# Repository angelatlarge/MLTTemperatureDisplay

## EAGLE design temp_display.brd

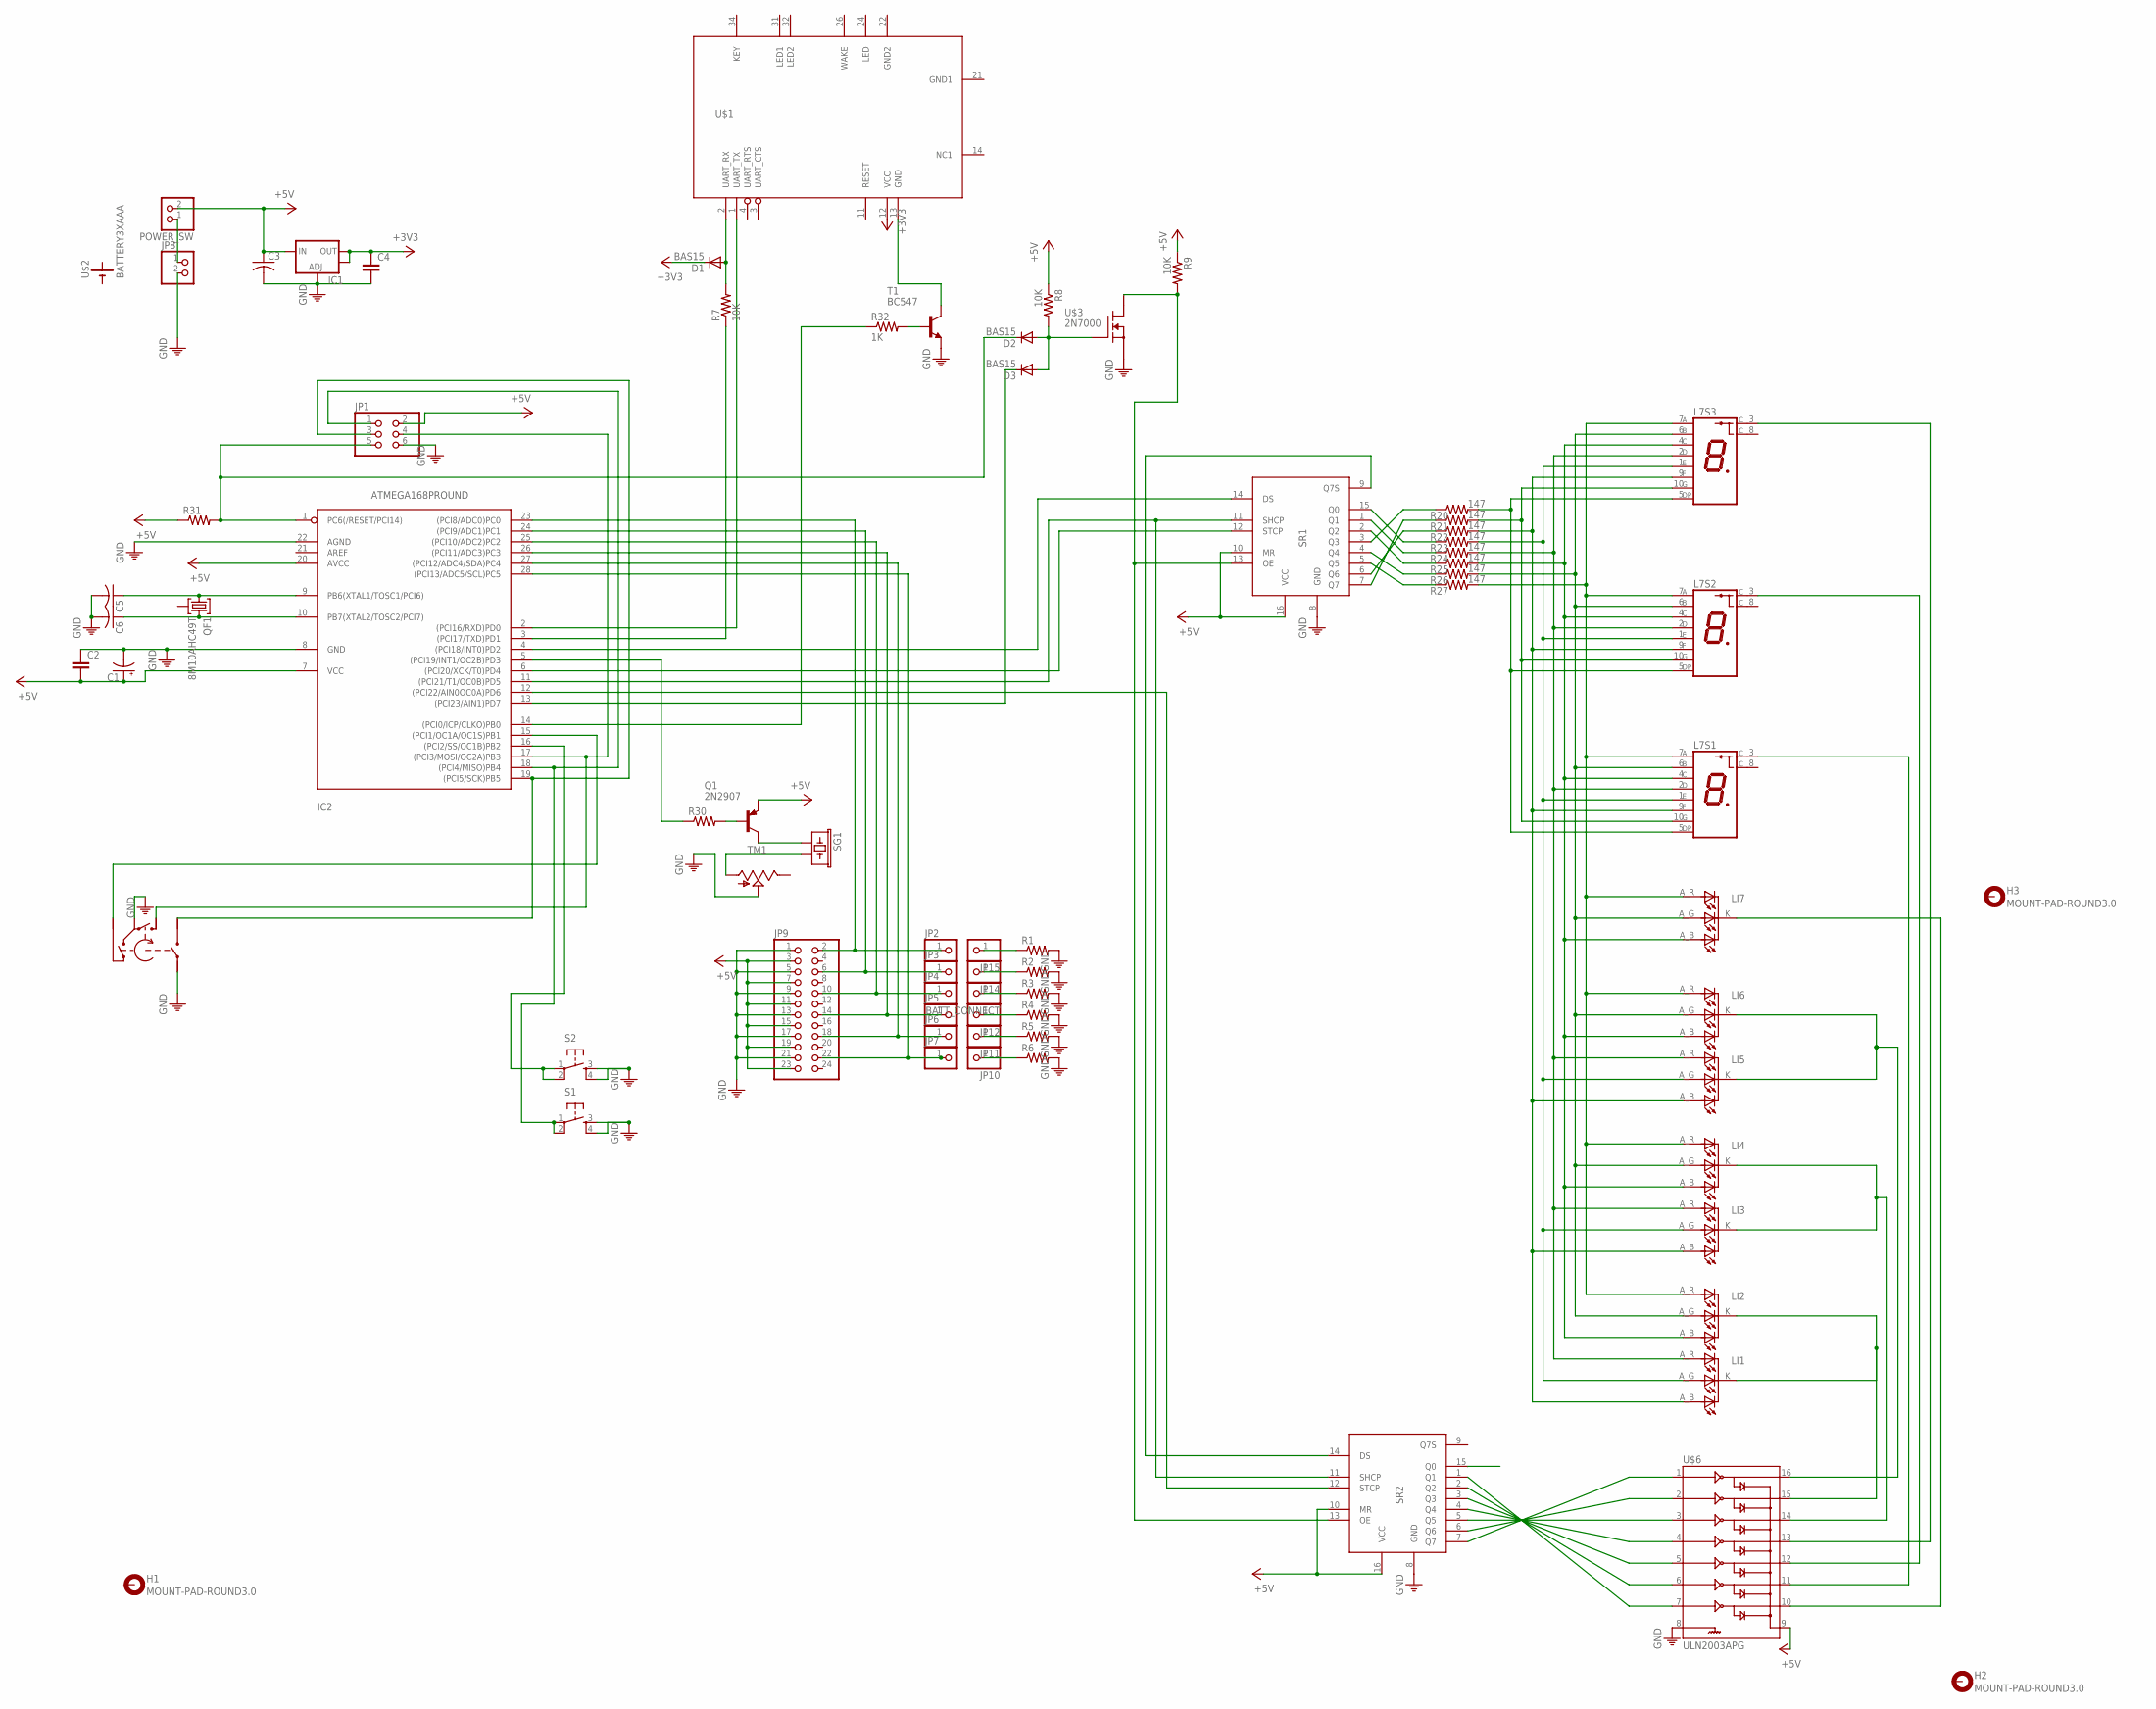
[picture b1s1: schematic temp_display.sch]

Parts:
BATT_CONNECT: PINHD-1X1; 1X01
C1: CPOL-USE2.5-5; E2,5-5
C2: CAPPTH1; CAP-PTH-5MM
C3: C-US050-025X075; C050-025X075
C4: CAPSMD; GRM43D
C5, C6: C-US025-024X044; C025-024X044
D1, D2, D3: BAS15; DO34-7
H1, H2, H3: MOUNT-PAD-ROUND3.0; 3,0-PAD
IC1: V_REG_LM1117SOT223; SOT223
IC2: ATMEGA168PROUND; DIL28-3-ROUND
JP1: PINHD-2X3; 2X03
JP2, JP3, JP4, JP5, JP6, JP7, JP10, JP11, JP12, JP14, JP15: PINHD-1X1; 1X01
JP8: PINHD-1X2; 1X02
JP9: PINHD-2X12; 2X12
L7S1, L7S2, L7S3: 7-SEGMENT_LED_CCED_C.BA_FG; 7-SEGMENT_LED
LI1, LI2, LI3, LI4, LI5, LI6, LI7: LED_RGB_CC; LED_RGB_5MM_
POWER_SW: PINHD-1X2; 1X02
Q1: 2N2907; TO92-EBC-OVAL
QF1: 8M10AHC49T; HC49U
R1, R2, R3, R4, R5, R6: R-USR_POWER-15X8.5; R_POWER-15X8.5
R7: 10K; 0204/7
R8, R9: 10K; 0204V
R20, R21, R22, R23, R24, R25, R26, R27: 147; 0204/7
R30: R-US_0204/2V; 0204V
R31: R-US_0204/5; 0204/5
R32: 1K; 0204/7
S1, S2: TAC_SWITCHPTH; TACTILE-PTH
SG1: BUZZERPTH; BUZZER-12MM
SR1, SR2: 74HC595; DIL16
T1: BC547; TO92
TM1: TRIMPOT; TRIMPOT_A
U$1: BLUETOOTH_MODULE_DX_FEWPADS; BLUETOOTH_MODULE_DX_FEW_PADS
U$2: BATTERY3XAAA; BATTERY_HOLDER_3XAAA
U$3: 2N7000; TO-92
U$5: ALPHA-ROT-ENCODER; TW-700198
U$6: ULN2003APG; DIL16

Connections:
+3V3: C4.A (1), D1.C, IC1.2 (OUT), IC1.4 (OUT), U$1.12 (VCC)
+5V: C1.+, C2.2, C3.1, IC1.3 (IN), IC2.7 (VCC), IC2.20 (AVCC), JP1.2, JP9.3, JP9.7, JP9.11, JP9.15, JP9.19, JP9.23, POWER_SW.2, Q1.E, R8.1, R9.1, R31.1, SR1.10 (MR), SR1.16 (VCC), SR2.10 (MR), SR2.16 (VCC), U$6.9
ADC0: IC2.23 ((PCI8/ADC0)PC0), JP2.1, JP9.2
ADC1: IC2.24 ((PCI9/ADC1)PC1), JP3.1, JP9.6
ADC2: IC2.25 ((PCI10/ADC2)PC2), JP4.1, JP9.10
ADC3: IC2.26 ((PCI11/ADC3)PC3), JP5.1, JP9.14
ADC4: IC2.27 ((PCI12/ADC4/SDA)PC4), JP6.1, JP9.18
ADC5: IC2.28 ((PCI13/ADC5/SCL)PC5), JP7.1, JP9.22
BTH_PW_TRANS: IC2.14 ((PCI0/ICP/CLKO)PB0), R32.1
CAT_1: SR2.1 (Q1), U$6.7
CAT_2: SR2.2 (Q2), U$6.6
CAT_3: SR2.3 (Q3), U$6.5
CAT_4: SR2.4 (Q4), U$6.4
CAT_5: SR2.5 (Q5), U$6.3
CAT_6: SR2.6 (Q6), U$6.2
CAT_7: SR2.7 (Q7), U$6.1
DS: IC2.4 ((PCI18/INT0)PD2), SR1.14 (DS)
GND: C1.-, C2.1, C3.2, C4.C (2), C5.2, C6.2, IC1.1 (ADJ), IC2.8 (GND), IC2.22 (AGND), JP1.6, JP8.2, JP9.1, JP9.5, JP9.9, JP9.13, JP9.17, JP9.21, R1.P$2 (2), R2.P$2 (2), R3.P$2 (2), R4.P$2 (2), R5.P$2 (2), R6.P$2 (2), S1.3, S1.4, S2.3, S2.4, SR1.8 (GND), SR2.8 (GND), T1.1 (E), TM1.S, U$3.1 (S), U$5.P2 (COM), U$5.P4 (S1), U$6.8
GND1: U$1.21 (GND1)
GND2: U$1.22 (GND2)
K_IL12: LI1.K, LI2.K, U$6.15
K_IL34: LI3.K, LI4.K, U$6.14
K_IL567: LI5.K, LI6.K, U$6.16
K_L7S_1: L7S1.3 (C), U$6.11
K_L7S_2: L7S2.3 (C), U$6.12
K_L7S_3: L7S3.3 (C), U$6.13
MROUTE: IC2.19 ((PCI5/SCK)PB5), JP1.3, U$5.P5 (S2)
unnamed: SR1.9 (Q7S), SR2.14 (DS)
unnamed: R32.2, T1.2 (B)
unnamed: T1.3 (C), U$1.13 (GND)
unnamed: D1.A, R7.2, U$1.2 (UART_RX)
unnamed: IC2.16 ((PCI2/SS/OC1B)PB2), S2.1, S2.2
unnamed: SG1.- (2), TM1.A
unnamed: LI7.K, U$6.10
unnamed: IC2.5 ((PCI19/INT1/OC2B)PD3), R30.1
unnamed: C5.1, IC2.9 (PB6(XTAL1/TOSC1/PCI6)), QF1.1
unnamed: C6.1, IC2.10 (PB7(XTAL2/TOSC2/PCI7)), QF1.3
unnamed: D3.C, IC2.13 ((PCI23/AIN1)PD7)
unnamed: D2.A, D3.A, R8.2, U$3.2 (G)
unnamed: R20.1, SR1.3 (Q3)
unnamed: JP8.1, POWER_SW.1
unnamed: R26.1, SR1.4 (Q4)
unnamed: R25.1, SR1.2 (Q2)
unnamed: JP15.1, R1.P$1 (1)
unnamed: JP14.1, R2.P$1 (1)
unnamed: R24.1, SR1.1 (Q1)
unnamed: R23.1, SR1.15 (Q0)
unnamed: IC2.18 ((PCI4/MISO)PB4), JP1.1, S1.1, S1.2
unnamed: IC2.17 ((PCI3/MOSI/OC2A)PB3), JP1.4, U$5.P1 (B)
unnamed: BATT_CONNECT.1, R3.P$1 (1)
unnamed: JP12.1, R4.P$1 (1)
unnamed: JP11.1, R5.P$1 (1)
unnamed: JP10.1, R6.P$1 (1)
unnamed: R27.1, SR1.5 (Q5)
unnamed: IC2.15 ((PCI1/OC1A/OC1S)PB1), U$5.P3 (A)
unnamed: R21.1, SR1.7 (Q7)
unnamed: R22.1, SR1.6 (Q6)
unnamed: Q1.B, R30.2
unnamed: Q1.C, SG1.+ (1)
OE: R9.2, SR1.13 (OE), SR2.13 (OE), U$3.3 (D)
RESET: D2.C, IC2.1 (PC6(/RESET/PCI14)), JP1.5, R31.2
SEG_A: L7S1.7 (SEG_A), L7S2.7 (SEG_A), L7S3.7 (SEG_A), LI2.A_R (R), LI4.A_R (R), LI6.A_R (R), LI7.A_R (R), R27.2
SEG_B: L7S1.6 (SEG_B), L7S2.6 (SEG_B), L7S3.6 (SEG_B), LI2.A_G (G), LI4.A_G (G), LI6.A_G (G), LI7.A_G (G), R26.2
SEG_C: L7S1.4 (SEG_C), L7S2.4 (SEG_C), L7S3.4 (SEG_C), LI2.A_B (B), LI4.A_B (B), LI6.A_B (B), LI7.A_B (B), R25.2
SEG_D: L7S1.2 (SEG_D), L7S2.2 (SEG_D), L7S3.2 (SEG_D), LI1.A_R (R), LI3.A_R (R), LI5.A_R (R), R24.2
SEG_DP: L7S1.5 (SEG_DP), L7S2.5 (SEG_DP), L7S3.5 (SEG_DP), R20.2
SEG_E: L7S1.1 (SEG_E), L7S2.1 (SEG_E), L7S3.1 (SEG_E), LI1.A_G (G), LI3.A_G (G), LI5.A_G (G), R23.2
SEG_F: L7S1.9 (SEG_F), L7S2.9 (SEG_F), L7S3.9 (SEG_F), LI1.A_B (B), LI3.A_B (B), LI5.A_B (B), R22.2
SEG_G: L7S1.10 (SEG_G), L7S2.10 (SEG_G), L7S3.10 (SEG_G), R21.2
SERIAL_RX: IC2.3 ((PCI17/TXD)PD1), R7.1
SERIAL_TX: IC2.2 ((PCI16/RXD)PD0), U$1.1 (UART_TX)
SHCP: IC2.11 ((PCI21/T1/OC0B)PD5), SR1.11 (SHCP), SR2.11 (SHCP)
STCP1: IC2.6 ((PCI20/XCK/T0)PD4), SR1.12 (STCP)
STCP2: IC2.12 ((PCI22/AIN0OC0A)PD6), SR2.12 (STCP)

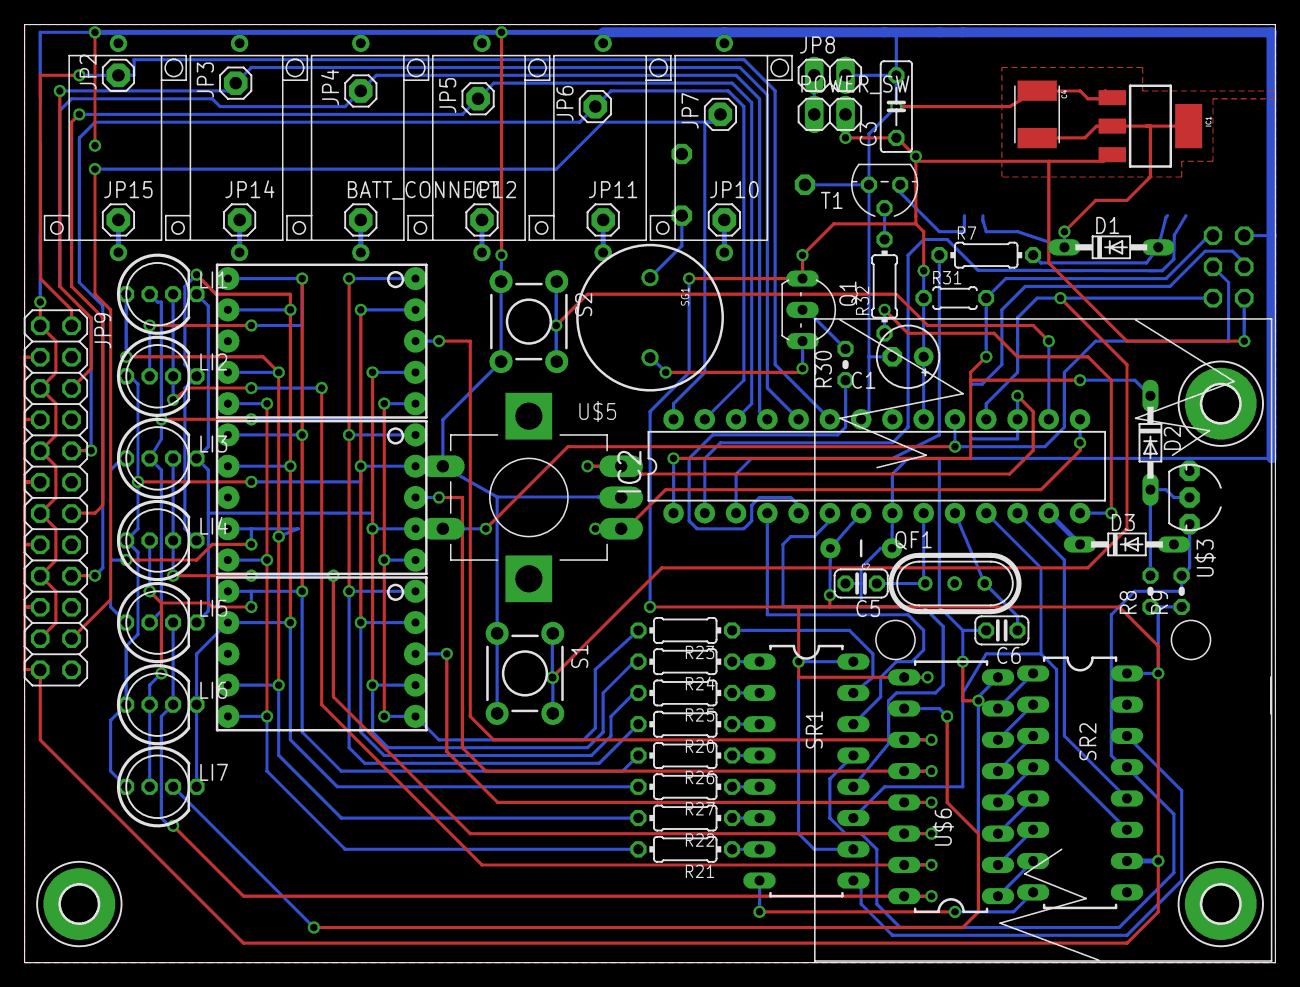
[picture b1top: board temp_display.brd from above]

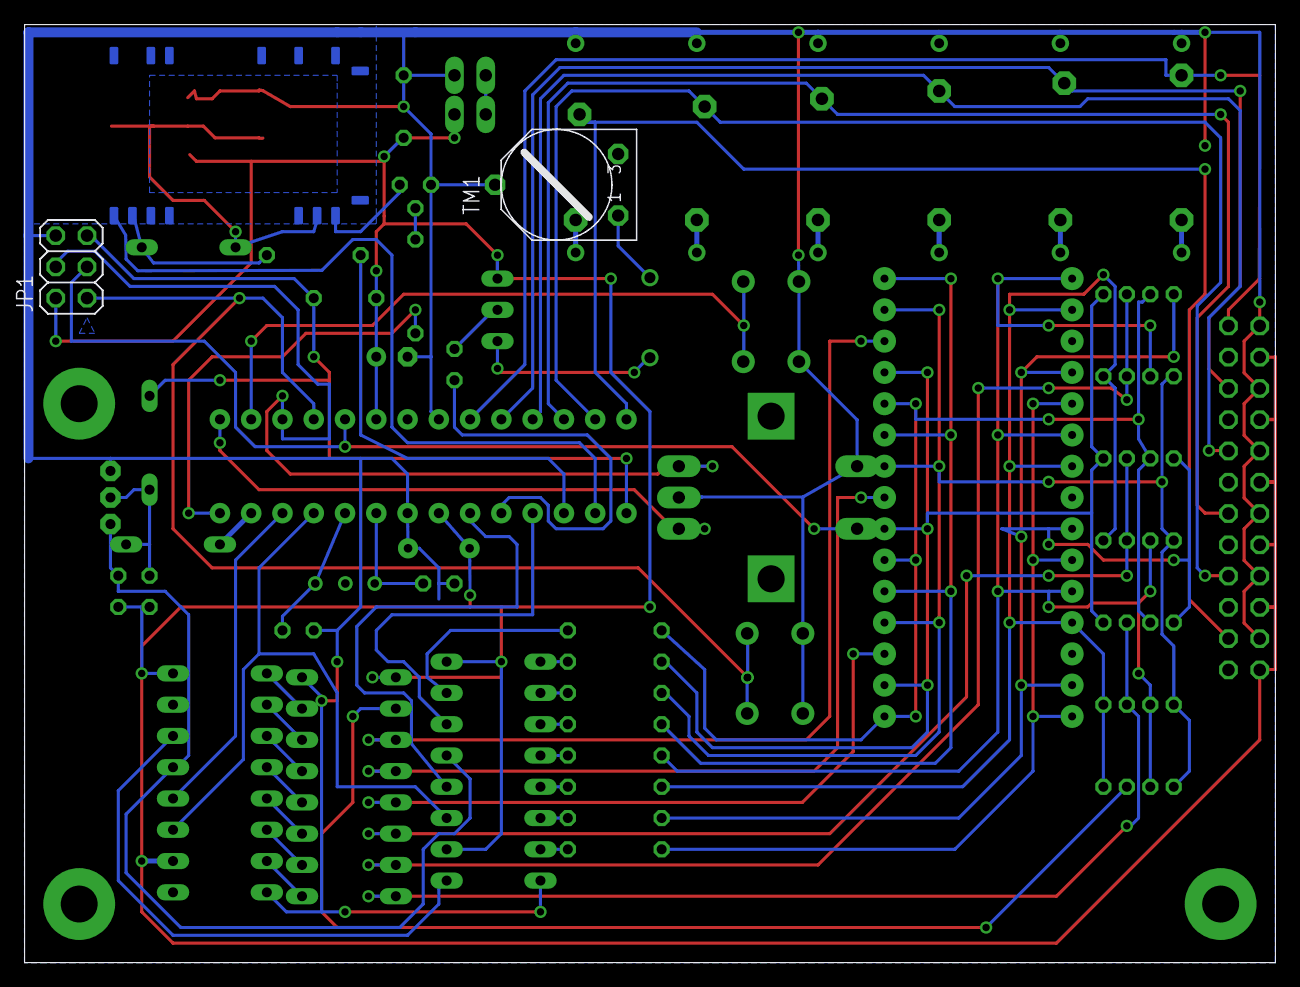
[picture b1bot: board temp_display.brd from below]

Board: 2 copper layers, 101.6 x 76.2 mm, 74 parts (3 on the bottom side), 72 nets.

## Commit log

2012-10-06 First version of the board
2012-10-07 The shift register seems to be working
2012-10-07 Preliminary version of the multi led program
2012-10-07 Imported routines for digit management from other temp_display
2012-10-07 Removed resistors from ULN2003 darlington array
2012-10-08 Bluetooth works!
2012-10-08 Fixed a number display bug.
2012-10-09 Added size to Makefile
2012-10-11 Intermediate version. Working on serial SR595
2012-10-11 Serial version now working
2012-10-11 Connected 595 shift registers serially.
2012-10-11 .gitignore and notes file
2012-10-11 Copied the value changing routine
2012-10-11 Intermediate version: working on the indicator LEDs
2012-10-23 Moved over to the library version of SR595
2012-10-23 In-progress version: indicators half-work
2012-10-24 Indicators are working well
2012-10-24 Speaker works
2012-10-24 Indicator color change for cycling/not cycling
2012-10-24 Timer1 now using consistent timebase
2012-10-24 Have a routine for setting indicators
2012-10-24 Timer works
2012-10-24 Beeps work, but the indicators are screwed up again.
2012-10-25 Encoder works OK now.
2012-10-25 Count-down timer and UI work pretty well.
2012-10-25 Timer sound now works
2012-10-25 Last version with CR2032 batteries
2012-10-28 Intermediate version. ADC does not work
2012-10-30 Temperature reading works.
2012-10-30 Bluetooth temperature updates work
2012-10-30 Bluetooth time display now works correctly. __delay__ timing is still off.
2012-10-31 Reworked the schematic to allow adding an external oscillator. Still need to build this on the proto board.
2012-11-01 OC2A still works as speaker output, but OC2B does not.
2012-11-01 Changed some sounds. OCR2B still doesn't work for output.
2012-11-01 Moved over the speaker to OCR2B
2012-11-01 Moved over to an external oscillator. Using 16-bit virtual ADC.
2012-11-01 Added startup "charge" sound
2012-11-01 Now reading bluetooth as well.
2012-11-01 Now shutting down the display during isploading. But the system isn't stable anymore.
2012-11-01 Fixed the bluetooth reading.
2012-11-07 Fixed some shorts. Now need to align indicators and code (wrong LEDs light up)
2012-11-08 New, object-oriented way of handling input Indicator software is set up correctly. Fixed tones.
2012-11-17 TH version of the pressure board is half-done
2012-11-17 New SMD version of the board
2012-11-19 The built pressure circuit.
2013-03-02 Copyright notice
2013-03-03 Working on volume display
2013-03-22 Pressure-based volume display should work now.
2013-03-24 Now displaying water level correctly
